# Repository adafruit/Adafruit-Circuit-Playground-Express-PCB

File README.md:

## Adafruit Circuit Playground Express PCB

<a href="http://www.adafruit.com/products/3333"><br/>
Click here to purchase one from the Adafruit shop</a>

PCB files for the Adafruit Circuit Playground Express. Format is EagleCAD schematic and board layout

For more details, check out the product page at
* http://www.adafruit.com/products/3333

### Description

Circuit Playground Express is the next step towards a perfect introduction to electronics and programming. We've taken the original Circuit Playground Classic and made it even better! Not only did we pack even more sensors in, we also made it even easier to program.

Start your journey with Microsoft MakeCode block-based or Javascript programming. Then, you can use the same board to try CircuitPython, with the Python interpreter running right on the Express. As you progress, you can advance to using Arduino IDE, which has full support of all the hardware down to the low level, so you can make powerful projects.You can even use code.org CS Discoveries to learn all about coding right in your browser!

Check out our detailed guide with a tour of Circuit Playground Express and details on getting started using MakeCode, CircuitPython, code.org CS Discoveries or Arduino!

Because you can program the same board in 4 different ways - the Express has great value and re-usability. From beginners to experts, Circuit Playground Express has something for everyone. If you are looking for our original, Arduino-only Circuit Playground, check out the Circuit Playground Classic.

The board is round and has alligator-clip pads around it so you don't have to solder or sew to make it work. You can power it from USB, a AAA battery pack, or with a Lipoly battery (for advanced users). Circuit Playground Express has built-in USB support. Built in USB means you plug it in to program it and it just shows up, no special cable or adapter required. Just program your code into the board then take it on the go!

### License

Adafruit invests time and resources providing this open source design, please support Adafruit and open-source hardware by purchasing products from [Adafruit](https://www.adafruit.com)!

Designed by Limor Fried/Ladyada for Adafruit Industries.

Creative Commons Attribution/Share-Alike, all text above must be included in any redistribution. See license.txt for additional details.

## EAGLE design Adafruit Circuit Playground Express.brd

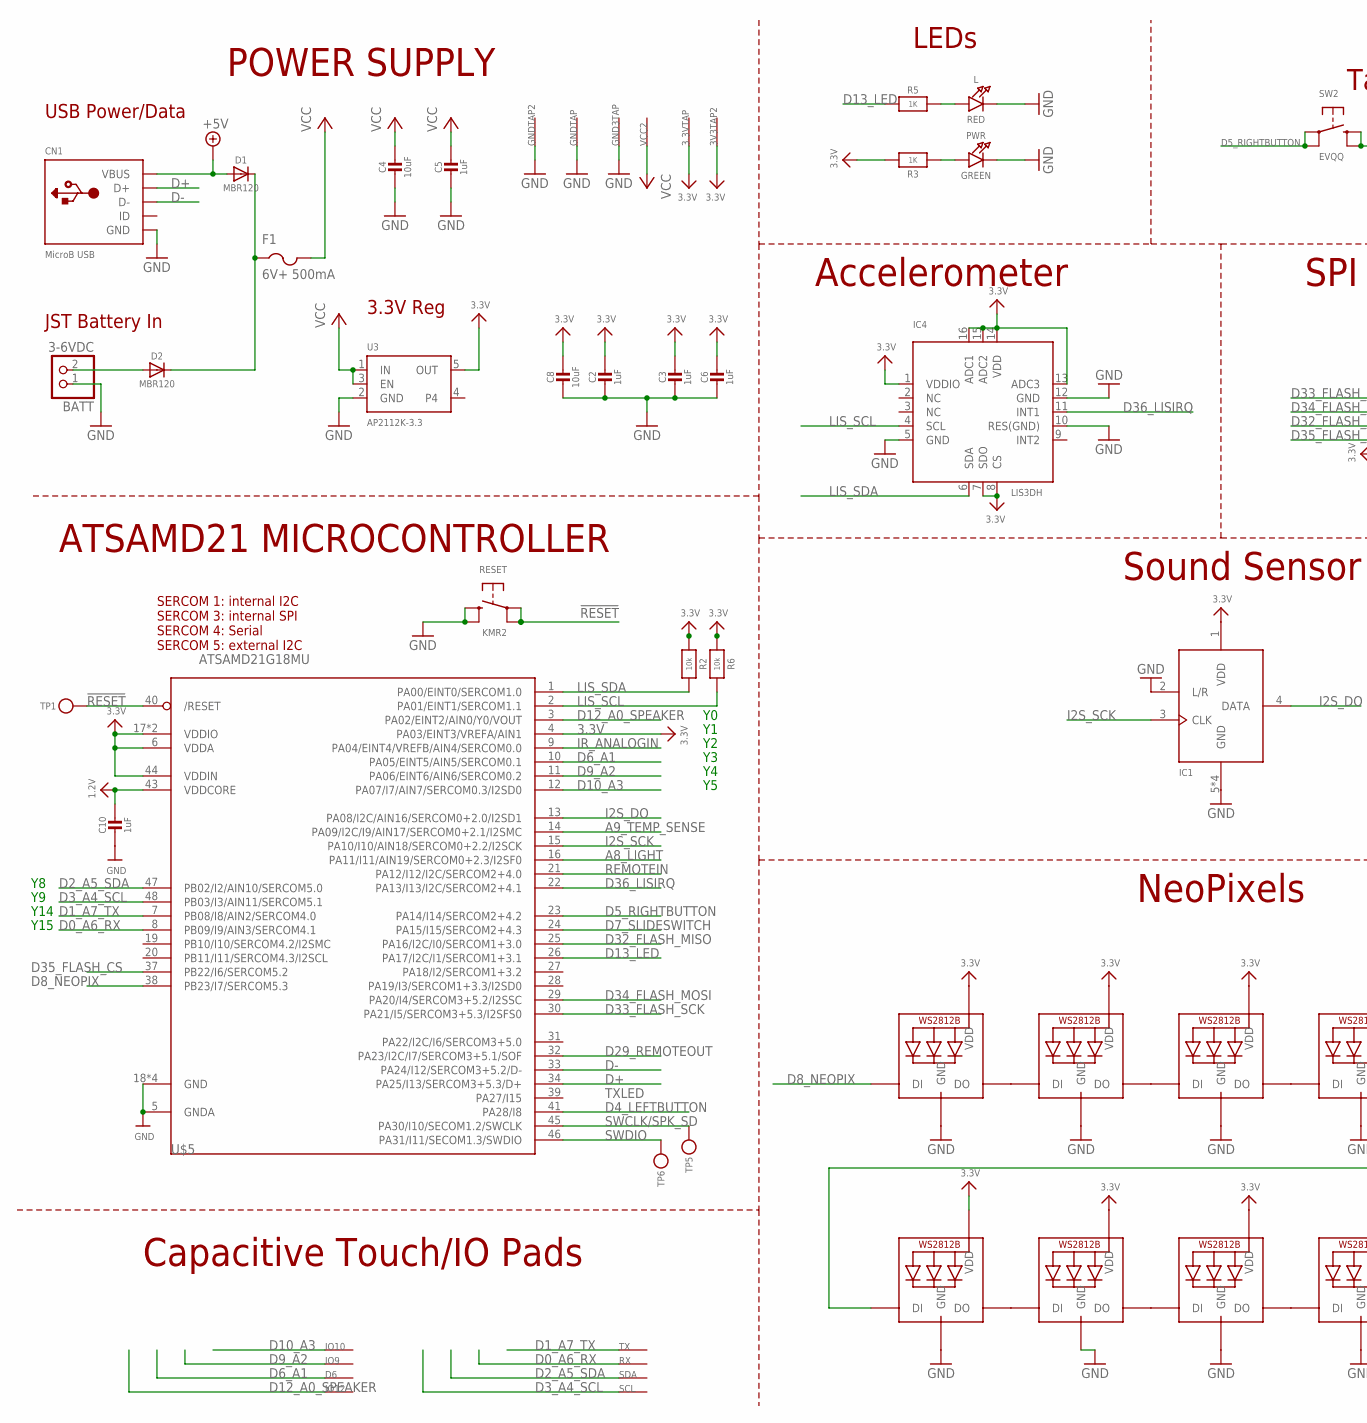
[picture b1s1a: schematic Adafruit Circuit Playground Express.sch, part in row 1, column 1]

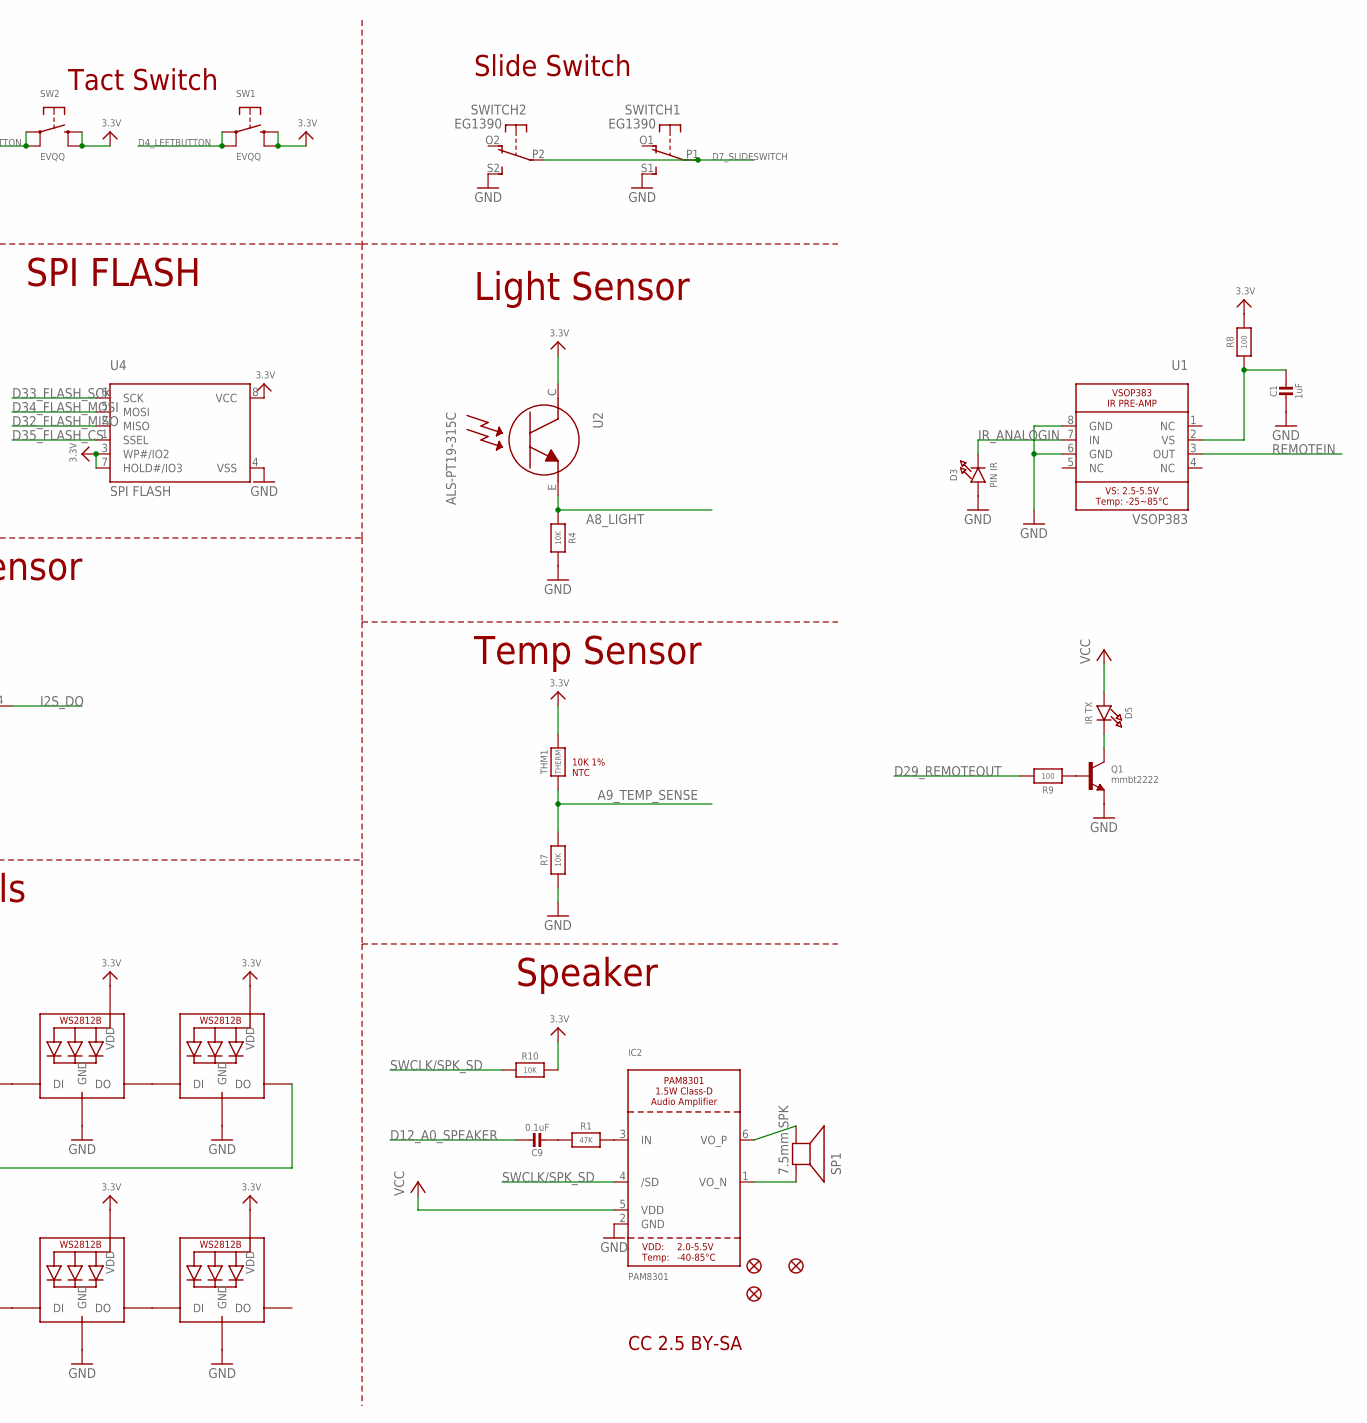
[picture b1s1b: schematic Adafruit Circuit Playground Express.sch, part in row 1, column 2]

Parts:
3.3VTAP, 3V3TAP2: SEWTAP-ALLIGATOR; SEWALLI
BATT: 3-6VDC; JSTPH2
C1, C2, C3, C5, C6, C10: 1uF; 0603-NO
C4, C8: 10uF; 0805-NO
C9: 0.1uF; 0603-NO
CN1: MicroB USB; 4UCONN_20329_V2
D1, D2: MBR120; SOD-123
D3: PIN IR; CHIPLED_1206_NOOUTLINE
D5: IR TX; CHIPLED_1206_NOOUTLINE
D6: SEWTAP-ALLIGATOR; SEWALLI
F1: 6V+ 500mA; R1206
GND3TAP: SEWTAP-ALLIGATOR; SEWALLI
GNDTAP, GNDTAP2: SEWTAP-ALLIGATOR; SEWALLI
IC1: MIC_PDM; SPK0415HM4H
IC2: PAM8301; SOT23-6
IC4: LIS3DH; LGA16_3X3MM
IO9, IO10, IO12: SEWTAP-ALLIGATOR; SEWALLI
L: RED; CHIPLED_0805_NOOUTLINE
LED1, LED2, LED3, LED4, LED5, LED6, LED7, LED8, LED9, LED10: WS2812B3535; LED3535
PWR: GREEN; CHIPLED_0805_NOOUTLINE
Q1: mmbt2222; SOT23-R
R1: 47K; 0603-NO
R2, R6: 10k; 0603-NO
R3, R5: 1K; 0603-NO
R4, R7, R10: 10K; 0603-NO
R8, R9: 100; 0603-NO
RESET: KMR2; BTN_KMR2_4.6X2.8
RX: SEWTAP-ALLIGATOR; SEWALLI
SCL: SEWTAP-ALLIGATOR; SEWALLI
SDA: SEWTAP-ALLIGATOR; SEWALLI
SP1: 7.5mm SPK; BUZZER_SMT_7.5MM
SW1, SW2: EVQQ; EVQ-Q2_SMALLER
SWITCH: EG1390
THM1: THERM; _0402
TP1, TP5, TP6: TESTPOINTROUND1.5MM; TESTPOINT_ROUND_1.5MM
TX: SEWTAP-ALLIGATOR; SEWALLI
U1: VSOP383
U2: ALS-PT19-315C
U3: AP2112K-3.3; SOT23-5
U4: SPI FLASH; SOIC8_150MIL
U$2, U$3, U$6: FIDUCIAL_1MM
U$5: ATSAMD21G18MU; TQFN48_7MM
VCC2: SEWTAP-ALLIGATOR; SEWALLI

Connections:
1.2V: C10.1, U$5.43 (VDDCORE)
3.3V: 3.3VTAP.P$1, 3V3TAP2.P$1, C2.1, C3.1, C6.1, C8.1, IC1.1 (VDD), IC4.1 (VDDIO), IC4.7 (SDO), IC4.8 (CS), IC4.13 (ADC3), IC4.14 (VDD), IC4.15 (ADC2), IC4.16 (ADC1), LED1.2 (VDD), LED2.2 (VDD), LED3.2 (VDD), LED4.2 (VDD), LED5.2 (VDD), LED6.2 (VDD), LED7.2 (VDD), LED8.2 (VDD), LED9.2 (VDD), LED10.2 (VDD), R2.1, R3.2, R6.1, R8.2, R10.2, SW1.B (S), SW1.B' (S1), SW2.B (S), SW2.B' (S1), THM1.2, U2.C, U3.5 (OUT), U4.3 (WP#/IO2), U4.7 (HOLD#/IO3), U4.8 (VCC), U$5.4 (PA03/EINT3/VREFA/AIN1), U$5.6 (VDDA), U$5.17 (VDDIO), U$5.36 (VDDIO), U$5.44 (VDDIN)
!RESET: RESET.A, RESET.A' (P1), TP1.P$1, U$5.40 (/RESET)
+5V: CN1.VBUS, D1.A
A8_LIGHT: R4.2, U2.E, U$5.16 (PA11/I11/AIN19/SERCOM0+2.3/I2SF0)
A9_TEMP_SENSE: R7.2, THM1.1, U$5.14 (PA09/I2C/I9/AIN17/SERCOM0+2.1/I2SMC)
D0_A6_RX: RX.P$1, U$5.8 (PB09/I9/AIN3/SERCOM4.1)
D1_A7_TX: TX.P$1, U$5.7 (PB08/I8/AIN2/SERCOM4.0)
D2_A5_SDA: SDA.P$1, U$5.47 (PB02/I2/AIN10/SERCOM5.0)
D3_A4_SCL: SCL.P$1, U$5.48 (PB03/I3/AIN11/SERCOM5.1)
D4_LEFTBUTTON: SW1.A, SW1.A' (P1), U$5.41 (PA28/I8)
D5_RIGHTBUTTON: SW2.A, SW2.A' (P1), U$5.23 (PA14/I14/SERCOM2+4.2)
D6_A1: D6.P$1, U$5.10 (PA05/EINT5/AIN5/SERCOM0.1)
D7_SLIDESWITCH: SWITCH.P1, SWITCH.P2, U$5.24 (PA15/I15/SERCOM2+4.3)
D8_NEOPIX: LED6.1 (DI), U$5.38 (PB23/I7/SERCOM5.3)
D9_A2: IO9.P$1, U$5.11 (PA06/EINT6/AIN6/SERCOM0.2)
D10_A3: IO10.P$1, U$5.12 (PA07/I7/AIN7/SERCOM0.3/I2SD0)
D12_A0_SPEAKER: C9.1, IO12.P$1, U$5.3 (PA02/EINT2/AIN0/Y0/VOUT)
D13_LED: R5.1, U$5.26 (PA17/I2C/I1/SERCOM1+3.1)
D29_REMOTEOUT: R9.2, U$5.32 (PA23/I2C/I7/SERCOM3+5.1/SOF)
D32_FLASH_MISO: U4.2 (MISO), U$5.25 (PA16/I2C/I0/SERCOM1+3.0)
D33_FLASH_SCK: U4.6 (SCK), U$5.30 (PA21/I5/SERCOM3+5.3/I2SFS0)
D34_FLASH_MOSI: U4.5 (MOSI), U$5.29 (PA20/I4/SERCOM3+5.2/I2SSC)
D35_FLASH_CS: U4.1 (SSEL), U$5.37 (PB22/I6/SERCOM5.2)
D36_LISIRQ: IC4.11 (INT1), U$5.22 (PA13/I13/I2C/SERCOM2+4.1)
D+: CN1.D+, U$5.34 (PA25/I13/SERCOM3+5.3/D+)
D-: CN1.D-, U$5.33 (PA24/I12/SERCOM3+5.2/D-)
GND: BATT.1, C1.2, C2.2, C3.2, C4.2, C5.2, C6.2, C8.2, C10.2, CN1.BASE@1 (GND), CN1.BASE@2 (GND), CN1.GND, CN1.SPRT@1 (GND), CN1.SPRT@2 (GND), CN1.SPRT@3 (GND), CN1.SPRT@4 (GND), D3.A, GND3TAP.P$1, GNDTAP.P$1, GNDTAP2.P$1, IC1.2 (L/R), IC1.5 (GND), IC1.6 (GND), IC1.7 (GND), IC1.8 (GND), IC2.2 (GND), IC4.5 (GND), IC4.10 (RES(GND)), IC4.12 (GND), L.C, LED1.4 (GND), LED2.4 (GND), LED3.4 (GND), LED4.4 (GND), LED5.4 (GND), LED6.4 (GND), LED7.4 (GND), LED8.4 (GND), LED9.4 (GND), LED10.4 (GND), PWR.C, Q1.2 (E), R4.1, R7.1, RESET.B (S), RESET.B' (S1), SWITCH.S1 (S), SWITCH.S2 (S), U1.6 (GND), U1.8 (GND), U3.2 (GND), U4.4 (VSS), U$5.5 (GNDA), U$5.18 (GND), U$5.35 (GND), U$5.42 (GND), U$5.THERMAL (GND)
I2S_DO: IC1.4 (DATA), U$5.13 (PA08/I2C/AIN16/SERCOM0+2.0/I2SD1)
I2S_SCK: IC1.3 (CLK), U$5.15 (PA10/I10/AIN18/SERCOM0+2.2/I2SCK)
IR_ANALOGIN: D3.C, U1.7 (IN), U$5.9 (PA04/EINT4/VREFB/AIN4/SERCOM0.0)
LIS_SCL: IC4.4 (SCL), R6.2, U$5.2 (PA01/EINT1/SERCOM1.1)
LIS_SDA: IC4.6 (SDA), R2.2, U$5.1 (PA00/EINT0/SERCOM1.0)
unnamed: PWR.A, R3.1
unnamed: C1.1, R8.1, U1.2 (VS)
unnamed: D1.C, D2.C, F1.1
unnamed: Q1.1 (B), R9.1
unnamed: C9.2, R1.1
unnamed: BATT.2, D2.A
unnamed: IC2.3 (IN), R1.2
unnamed: IC2.6 (VO_P), SP1.-
unnamed: L.A, R5.2
unnamed: LED1.1 (DI), LED2.3 (DO)
unnamed: LED1.3 (DO), LED3.1 (DI)
unnamed: LED2.1 (DI), LED10.3 (DO)
unnamed: LED6.3 (DO), LED7.1 (DI)
unnamed: IC2.1 (VO_N), SP1.+
unnamed: LED7.3 (DO), LED8.1 (DI)
unnamed: LED8.3 (DO), LED9.1 (DI)
unnamed: LED9.3 (DO), LED10.1 (DI)
unnamed: LED3.3 (DO), LED4.1 (DI)
unnamed: LED4.3 (DO), LED5.1 (DI)
unnamed: D5.C, Q1.3 (C)
REMOTEIN: U1.3 (OUT), U$5.21 (PA12/I12/I2C/SERCOM2+4.0)
SWCLK/SPK_SD: IC2.4 (/SD), R10.1, TP5.P$1, U$5.45 (PA30/I10/SECOM1.2/SWCLK)
SWDIO: TP6.P$1, U$5.46 (PA31/I11/SECOM1.3/SWDIO)
VCC: C4.1, C5.1, D5.A, F1.2, IC2.5 (VDD), U3.1 (IN), U3.3 (EN), VCC2.P$1

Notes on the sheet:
CC 2.5 BY-SA
10K 1% NTC
ATSAMD21 MICROCONTROLLER
USB Power/Data
JST Battery In
3.3V Reg
POWER SUPPLY
NeoPixels
Speaker
Temp Sensor
Light Sensor
Sound Sensor
Slide Switch
Tact Switch
LEDs
Accelerometer
TXLED
SERCOM 1: internal I2C SERCOM 3: internal SPI SERCOM 4: Serial SERCOM 5: external I2C
Y14
Y15
Capacitive Touch/IO Pads
SPI FLASH

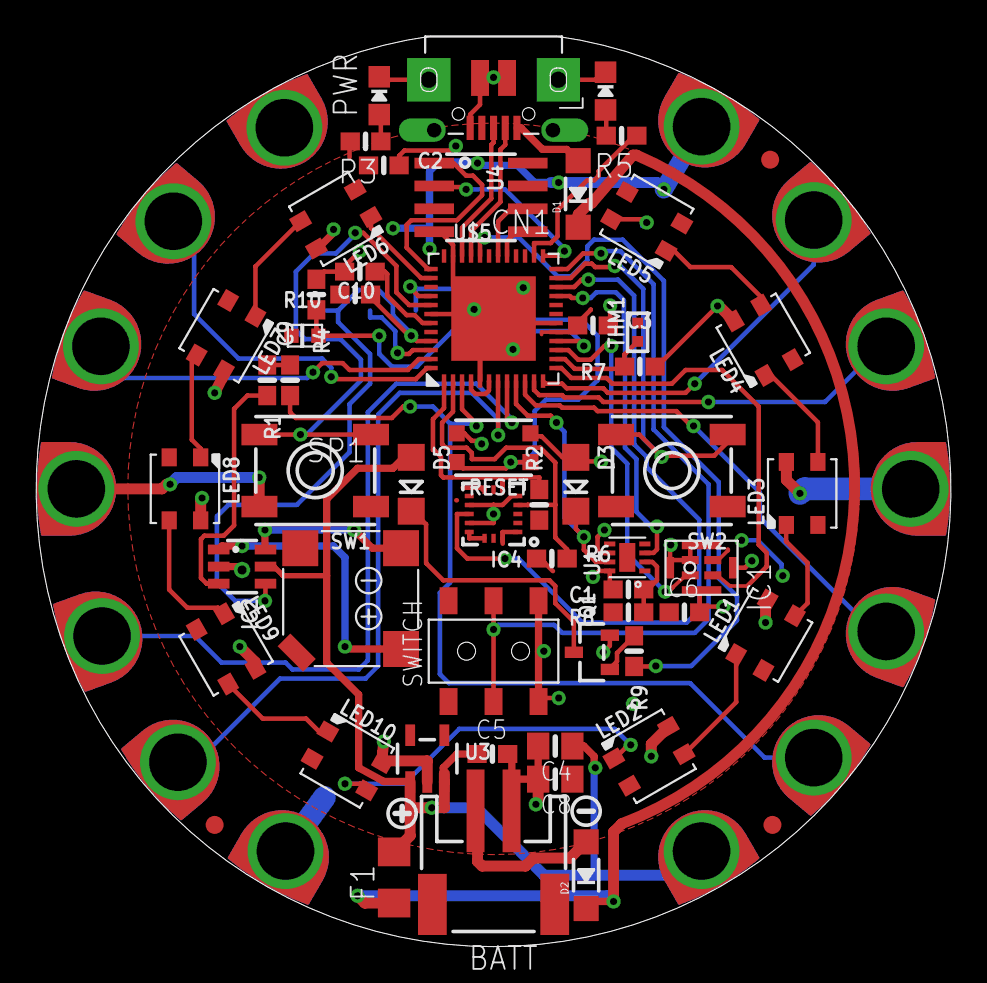
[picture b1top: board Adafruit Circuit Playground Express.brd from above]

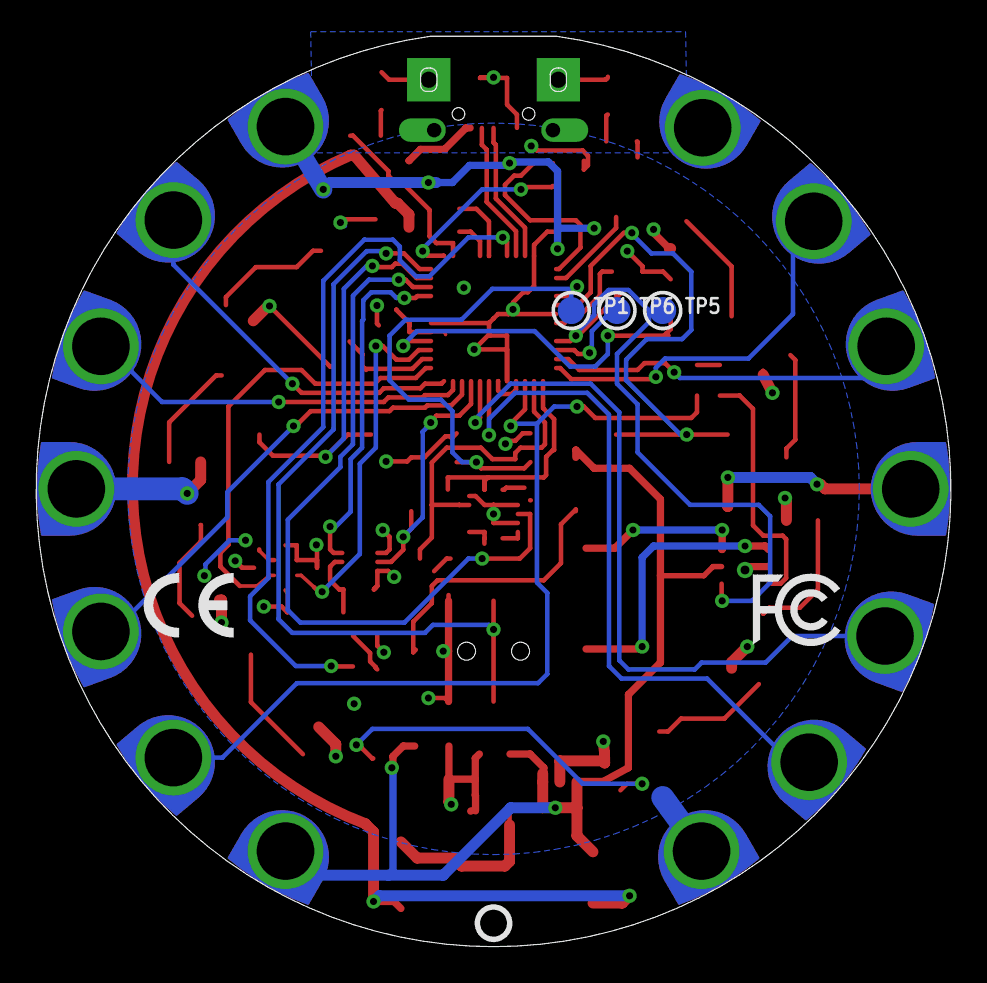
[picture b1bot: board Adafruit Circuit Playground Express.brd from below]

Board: 2 copper layers, 50.8 x 50.6 mm, 81 parts (8 on the bottom side), 57 nets.

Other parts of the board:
U$1: SYMBOL_MINUS
U$4: FLORAMED
U$7: PCBFEAT-REV-040
U$16: CPLAY_EXPRESS_FRONT_REVG
U$33: SYMBOL_FCC_5MM
U$34: SYMBOL_CE_5MM
U$35: SYMBOL_PLUS
U$46: CPLAY_EXPRESS_BACK_REVD

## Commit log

2017-06-14 woo we're shipping!
2025-09-24 Change battery connector

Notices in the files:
parts and their libraries:
microbuilder: This work is placed in the public domain, and may be freely used for commercial and non-commercial work with the following conditions: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
